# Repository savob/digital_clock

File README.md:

# Digital Clock
A hardware only digital clock project, my first embedded project without a single microcontroller involved!

Designed in a modular system to allow easy reconfiguration and expirimentation with each module. There are three modules:
1. Display module - These each carry a pair of LED seven segment character displays, their drivers, and a counter for each digit
2. Reset logic module - These recieve the data for a pair of digits and routes it through logic gates to determine if a digit needs to be reset (e.g. at 10)
3. Signal generator module - This generates the base 1 Hz signal used by the clock and provides the power for all other modules

### Small Notice
In the original designs of the reset modules I either forgot or naively didn't bother to include decoupling capacitors for the ICs. This caused the system to be incredibly suseptible to any sort of electrostatic discharge in the surrendings and throwing off the time.

This has been addressed in the newer version.

## Display Module
The main modules present; serve to house and drive two displays each as well as the counter for each digit. The digits are all standard LED seven-segment character displays and can be either common anode (CA) or common cathode (CC) types. The board can accomadate either by switching the driver chip used and a solder jumper accordingly. The left digit is referred to as the "primary" and the right one as "secondary".

The counters serve to store the value for each digit and increment it when they recieve a clock signal. When a digit "turns over" (returns to zero, resets) this is also used as the signal to increment the next digit up. The result is the count (time) is propagated right to left through the system like a normal clock. The logic to reset digits is not housed on these boards themselves, instead the signals for the value of each couter and their reset signal are routed to the bottom to be handled by the logic modules. 

## Reset Logic Module
This is responsible for "turning over" digits as needed when they reach their upper limit, 6 or 10 (with special cases for the hour digits). These have a set of four two-input AND and OR gates that are to be wired up by the user depending on the behavior desired for a given digit.

For example the ones digit for seconds needs to be reset everytime it reaches ten (10). To arrange for this the user would wire the 8 and 2 signal for that digit (8S and 2S respectively since it would be the secondary digit on that diplay) to the inputs of one of the AND gates available, then connect the output of that AND to the reset for that digit (RS). Now when it is 10 (8 + 2), the reset will be driven high and the counter will return to zero (and increment the next digit up).

## Signal Generator Module
This module serves two purposes: primarily to generate the required 1 Hz base clock for the clock, and secondarily to supply the system with the 5V required via a standard USB.

The 1 Hz signal is generated using a CD4060 chip driving a 32.768 kHz crystal and dividing down the signal by a factor of 256 to 128 Hz, which is fed into another CD4060 and divided down further by a factor of 128 to produce a steady 1 Hz that is fed into the clock.

### Software Used
KiCad EDA 6.0.1 was originally used to design all the schematics and boards. It has since been updated to KiCad 7.0.10.

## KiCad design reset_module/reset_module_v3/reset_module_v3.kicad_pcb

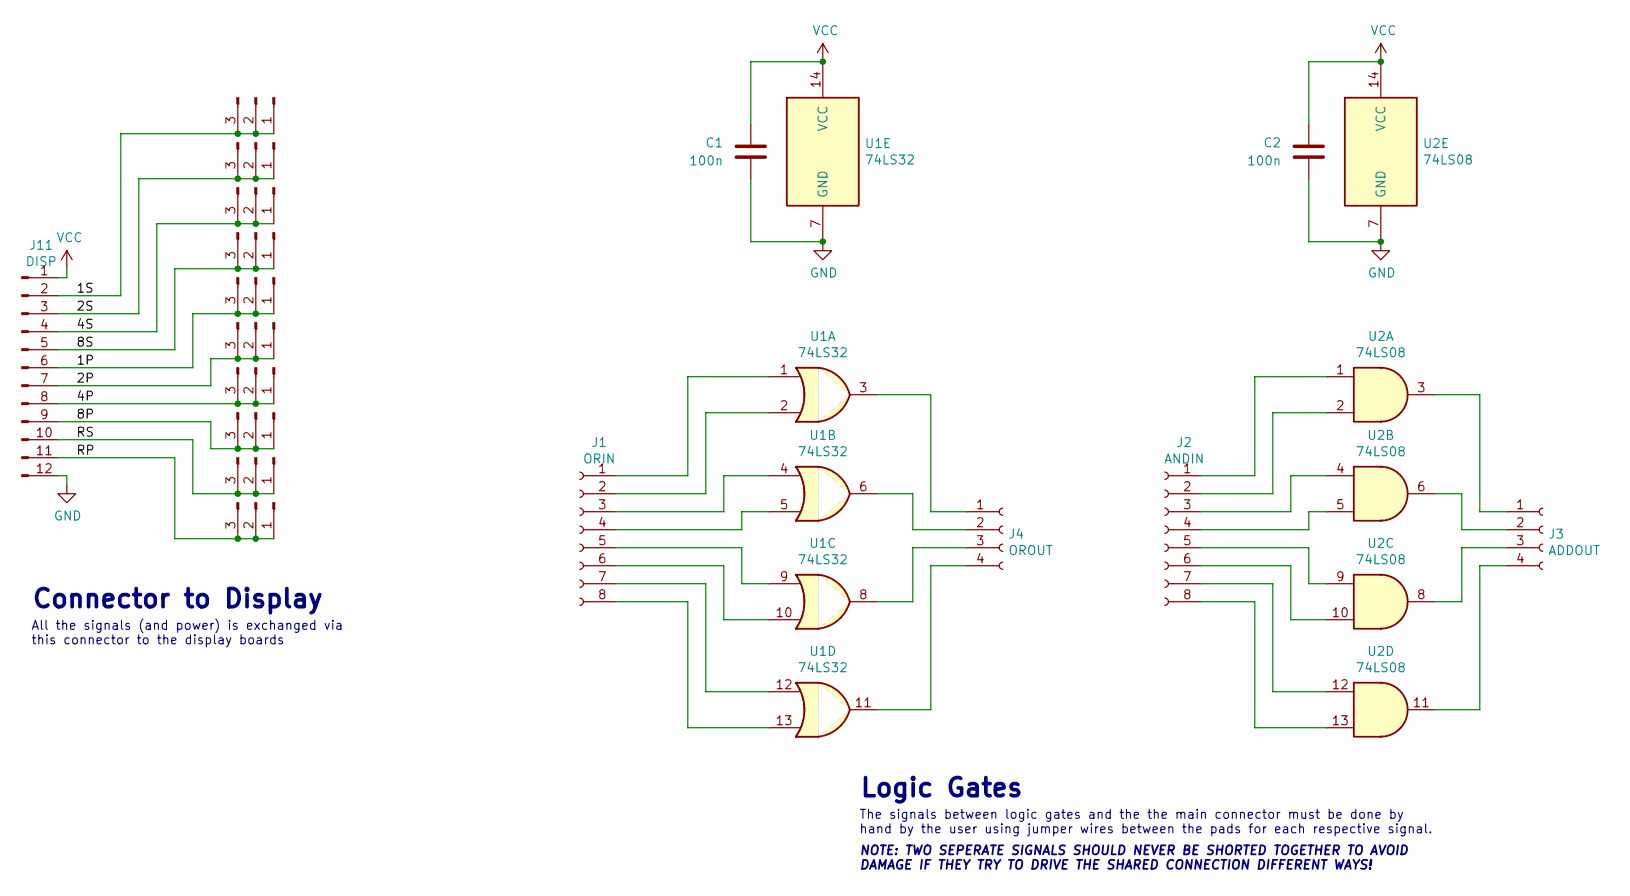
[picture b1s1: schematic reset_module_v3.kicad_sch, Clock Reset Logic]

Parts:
C1, C2: 100n; C_Disc_D3.8mm_W2.6mm_P2.50mm
J1: ORIN; PinHeader_1x08_P2.54mm_Vertical
J2: ANDIN; PinHeader_1x08_P2.54mm_Vertical
J3: ADDOUT; PinHeader_1x04_P2.54mm_Vertical
J4: OROUT; PinHeader_1x04_P2.54mm_Vertical
J5, J6, J7, J8, J9, J10, J12, J13, J14, J15: Conn_01x03_Male; PinHeader_1x03_P2.54mm_Vertical
J11: DISP; PinSocket_1x12_P2.54mm_Horizontal
U1: 74LS32; DIP-14_W7.62mm_Socket
U2: 74LS08; DIP-14_W7.62mm_Socket

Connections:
/1P: J9.1, J9.2, J9.3, J11.6
/1S: J5.1, J5.2, J5.3, J11.2
/2P: J10.1, J10.2, J10.3, J11.7
/2S: J6.1, J6.2, J6.3, J11.3
/4P: J11.8, J12.1, J12.2, J12.3
/4S: J7.1, J7.2, J7.3, J11.4
/8P: J11.9, J13.1, J13.2, J13.3
/8S: J8.1, J8.2, J8.3, J11.5
/RP: J11.11, J15.1, J15.2, J15.3
/RS: J11.10, J14.1, J14.2, J14.3
GND: C1.2, C2.2, J11.12, U1.7 (GND), U2.7 (GND)
unnamed: J1.1, U1.1
unnamed: J1.2, U1.2
unnamed: J1.3, U1.4
unnamed: J1.4, U1.5
unnamed: J1.5, U1.9
unnamed: J1.6, U1.10
unnamed: J1.7, U1.12
unnamed: J1.8, U1.13
unnamed: J2.1, U2.1
unnamed: J2.2, U2.2
unnamed: J2.3, U2.4
unnamed: J2.4, U2.5
unnamed: J2.5, U2.9
unnamed: J2.6, U2.10
unnamed: J2.7, U2.12
unnamed: J2.8, U2.13
unnamed: J3.1, U2.3
unnamed: J3.2, U2.6
unnamed: J3.3, U2.8
unnamed: J3.4, U2.11
unnamed: J4.1, U1.3
unnamed: J4.2, U1.6
unnamed: J4.3, U1.8
unnamed: J4.4, U1.11
VCC: C1.1, C2.1, J11.1, U1.14 (VCC), U2.14 (VCC)

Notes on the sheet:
Logic Gates
Connector to Display
NOTE: TWO SEPERATE SIGNALS SHOULD NEVER BE SHORTED TOGETHER TO AVOID DAMAGE IF THEY TRY TO DRIVE THE SHARED CONNECTION DIFFERENT WAYS!
The signals between logic gates and the the main connector must be done by hand by the user using jumper wires between the pads for each respective signal.
All the signals (and power) is exchanged via this connector to the display boards

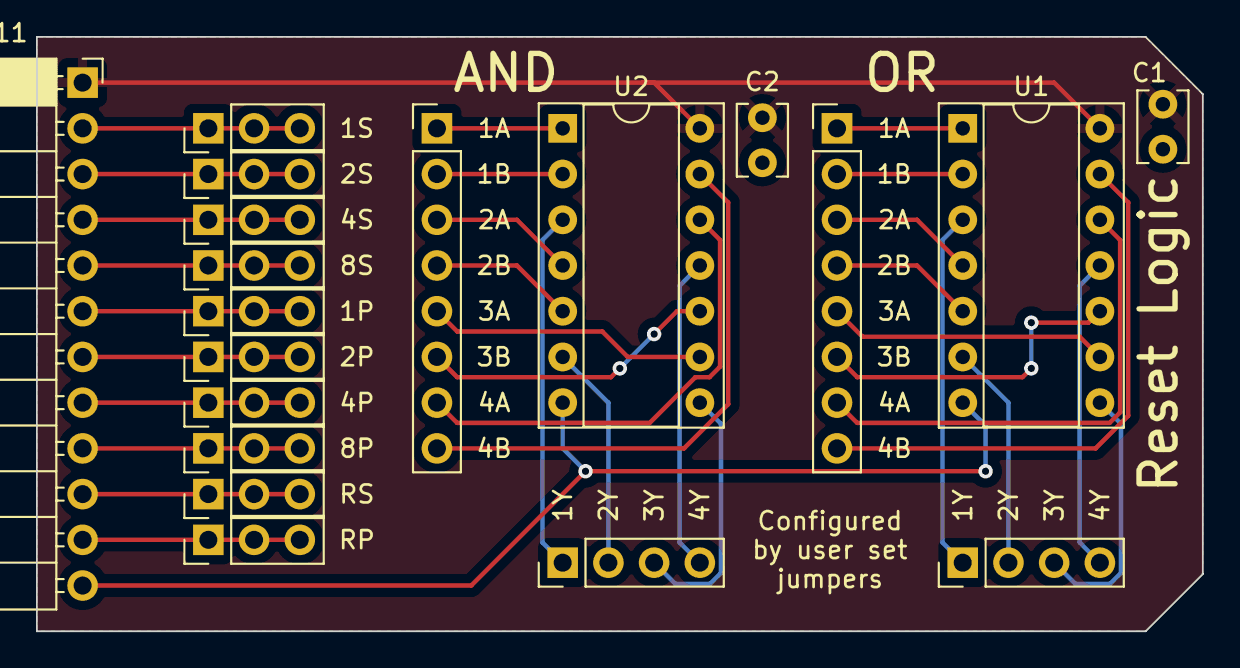
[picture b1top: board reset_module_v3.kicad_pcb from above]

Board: 2 copper layers, 64.8 x 33.0 mm, 19 parts (0 on the bottom side), 36 nets.

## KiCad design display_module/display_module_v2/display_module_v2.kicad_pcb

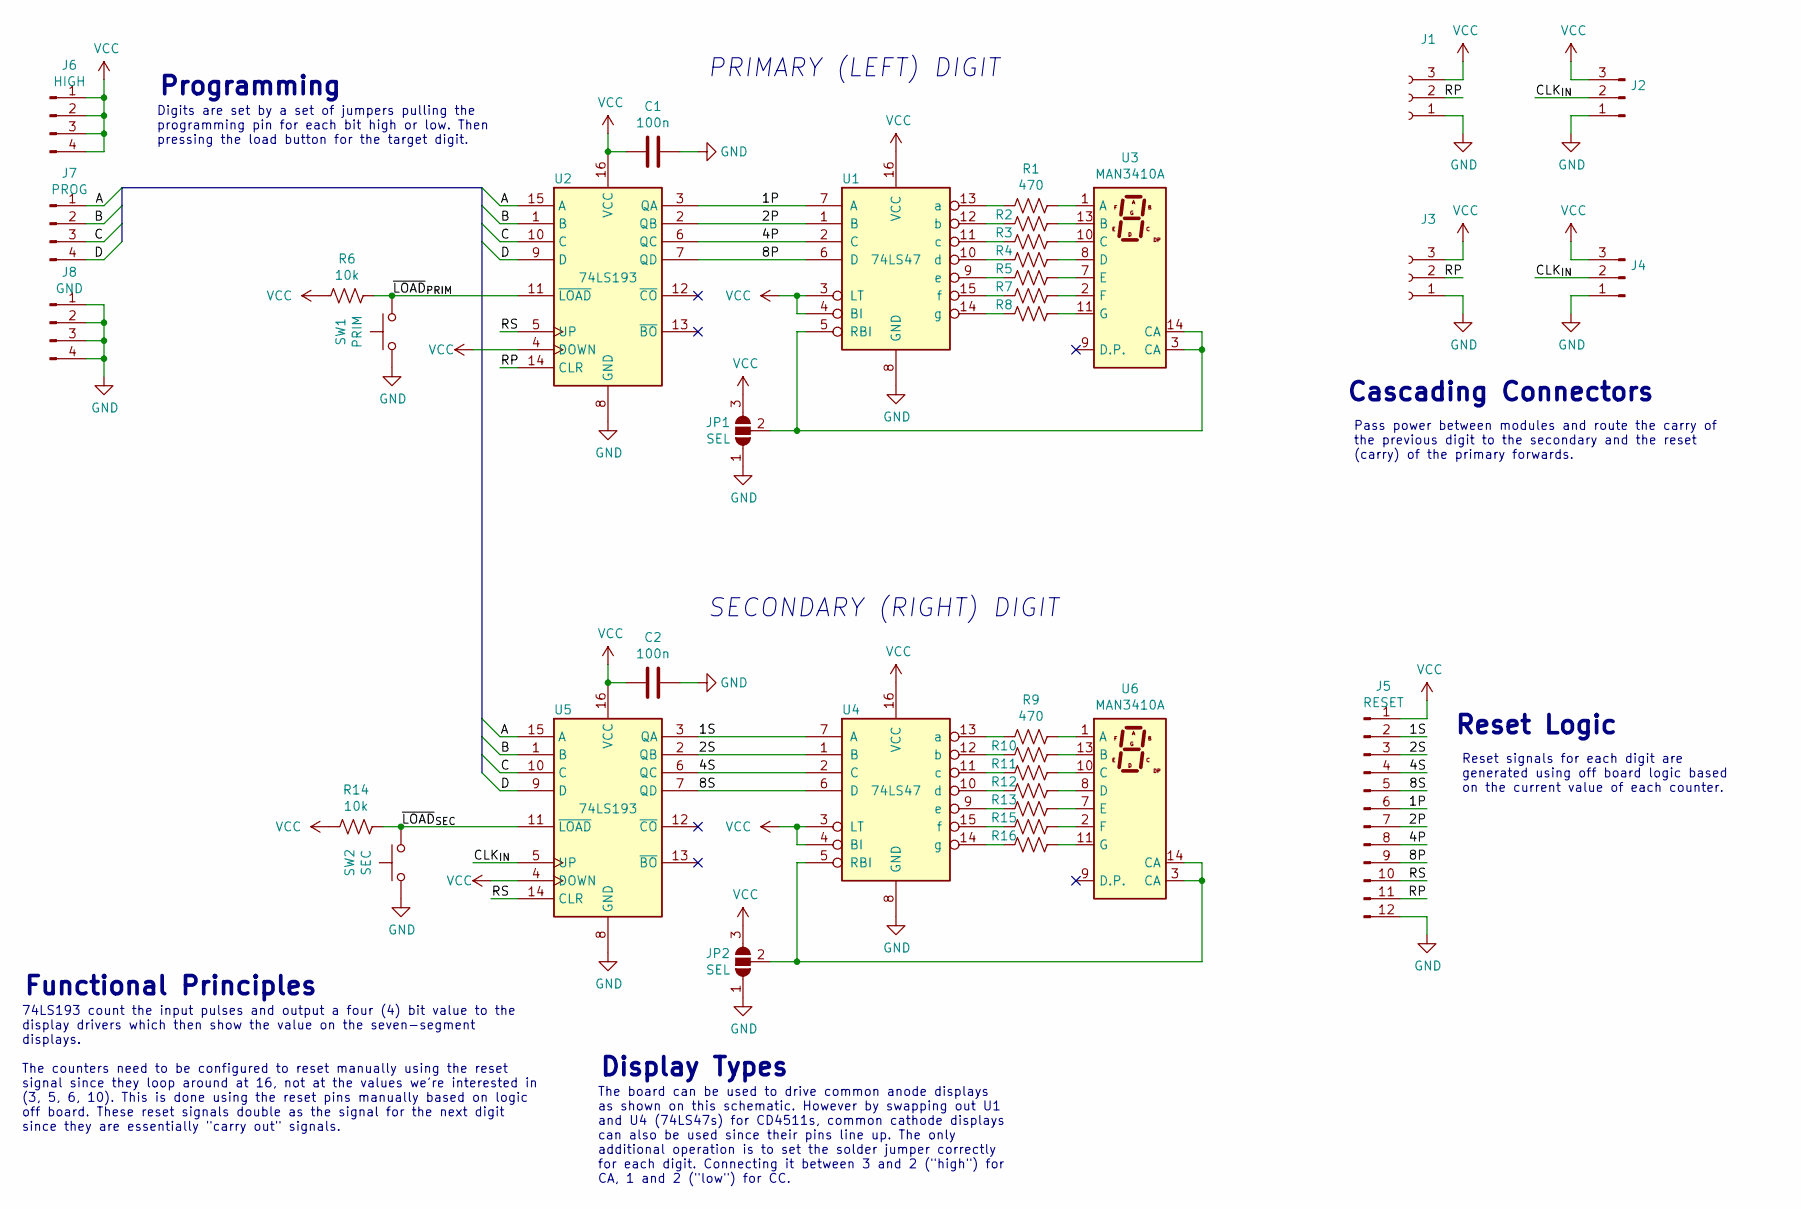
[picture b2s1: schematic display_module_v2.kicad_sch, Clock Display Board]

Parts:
C1, C2: 100n; C_Disc_D3.8mm_W2.6mm_P2.50mm
J1, J3: Conn_01x03_Female; PinSocket_1x03_P2.54mm_Horizontal
J2, J4: Conn_01x03_Male; PinHeader_1x03_P2.54mm_Horizontal
J5: RESET; PinHeader_1x12_P2.54mm_Horizontal
J6: HIGH; PinHeader_1x04_P2.54mm_Vertical
J7: PROG; PinHeader_1x04_P2.54mm_Vertical
J8: GND; PinHeader_1x04_P2.54mm_Vertical
JP1, JP2: SEL; SolderJumper-3_P1.3mm_Open_RoundedPad1.0x1.5mm
R1, R2, R3, R4, R5, R7, R8, R9, R10, R11, R12, R13, R15, R16: 470; R_Axial_DIN0207_L6.3mm_D2.5mm_P10.16mm_Horizontal
R6, R14: 10k; R_Axial_DIN0207_L6.3mm_D2.5mm_P10.16mm_Horizontal
SW1: PRIM; SW_PUSH_6mm_H4.3mm
SW2: SEC; SW_PUSH_6mm_H4.3mm
U1, U4: 74LS47; DIP-16_W7.62mm
U2, U5: 74LS193; DIP-16_W7.62mm
U3, U6: MAN3410A

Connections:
/1P: J5.6, U1.7 (A), U2.3 (QA)
/1S: J5.2, U4.7 (A), U5.3 (QA)
/2P: J5.7, U1.1 (B), U2.2 (QB)
/2S: J5.3, U4.1 (B), U5.2 (QB)
/4P: J5.8, U1.2 (C), U2.6 (QC)
/4S: J5.4, U4.2 (C), U5.6 (QC)
/8P: J5.9, U1.6 (D), U2.7 (QD)
/8S: J5.5, U4.6 (D), U5.7 (QD)
/A: J7.1, U2.15 (A), U5.15 (A)
/B: J7.2, U2.1 (B), U5.1 (B)
/C: J7.3, U2.10 (C), U5.10 (C)
/CLK_{IN}: J2.2, J4.2, U5.5 (UP)
/D: J7.4, U2.9 (D), U5.9 (D)
/RP: J1.2, J3.2, J5.11, U2.14 (CLR)
/RS: J5.10, U2.5 (UP), U5.14 (CLR)
/~LOAD_{PRIM}: R6.1, SW1.2, U2.11 (~LOAD)
/~LOAD_{SEC}: R14.1, SW2.2, U5.11 (~LOAD)
GND: C1.2, C2.2, J1.1, J2.1, J3.1, J4.1, J5.12, J8.1, J8.2, J8.3, J8.4, JP1.1 (A), JP2.1 (A), SW1.1, SW2.1, U1.8 (GND), U2.8 (GND), U4.8 (GND), U5.8 (GND)
unnamed: JP1.2 (C), U1.5 (RBI), U3.3 (CA), U3.14 (CA)
unnamed: JP2.2 (C), U4.5 (RBI), U6.3 (CA), U6.14 (CA)
unnamed: R1.1, U3.1 (A)
unnamed: R1.2, U1.13 (a)
unnamed: R2.1, U3.13 (B)
unnamed: R2.2, U1.12 (b)
unnamed: R3.1, U3.10 (C)
unnamed: R3.2, U1.11 (c)
unnamed: R4.1, U3.8 (D)
unnamed: R4.2, U1.10 (d)
unnamed: R5.1, U3.7 (E)
unnamed: R5.2, U1.9 (e)
unnamed: R7.1, U3.2 (F)
unnamed: R7.2, U1.15 (f)
unnamed: R8.1, U3.11 (G)
unnamed: R8.2, U1.14 (g)
unnamed: R9.1, U6.1 (A)
unnamed: R9.2, U4.13 (a)
unnamed: R10.1, U6.13 (B)
unnamed: R10.2, U4.12 (b)
unnamed: R11.1, U6.10 (C)
unnamed: R11.2, U4.11 (c)
unnamed: R12.1, U6.8 (D)
unnamed: R12.2, U4.10 (d)
unnamed: R13.1, U6.7 (E)
unnamed: R13.2, U4.9 (e)
unnamed: R15.1, U6.2 (F)
unnamed: R15.2, U4.15 (f)
unnamed: R16.1, U6.11 (G)
unnamed: R16.2, U4.14 (g)
VCC: C1.1, C2.1, J1.3, J2.3, J3.3, J4.3, J5.1, J6.1, J6.2, J6.3, J6.4, JP1.3 (B), JP2.3 (B), R6.2, R14.2, U1.3 (LT), U1.4 (BI), U1.16 (VCC), U2.4 (DOWN), U2.16 (VCC), U4.3 (LT), U4.4 (BI), U4.16 (VCC), U5.4 (DOWN), U5.16 (VCC)

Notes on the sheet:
Reset signals for each digit are generated using off board logic based on the current value of each counter.
Pass power between modules and route the carry of the previous digit to the secondary and the reset (carry) of the primary forwards.
74LS193 count the input pulses and output a four (4) bit value to the display drivers which then show the value on the seven-segment displays. The counters need to be configured to reset manually using the reset signal since they loop around at 16, not at the values we're interested in (3, 5, 6, 10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
Digits are set by a set of jumpers pulling the programming pin for each bit high or low. Then pressing the load button for the target digit.
The board can be used to drive common anode displays as shown on this schematic. However by swapping out U1 and U4 (74LS47s) for CD4511s, common cathode displays can also be used since their pins line up. The only additional operation is to set the solder jumper correctly for each digit. Connecting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
Functional Principles
Programming
PRIMARY (LEFT) DIGIT
Reset Logic
SECONDARY (RIGHT) DIGIT
Display Types
Cascading Connectors

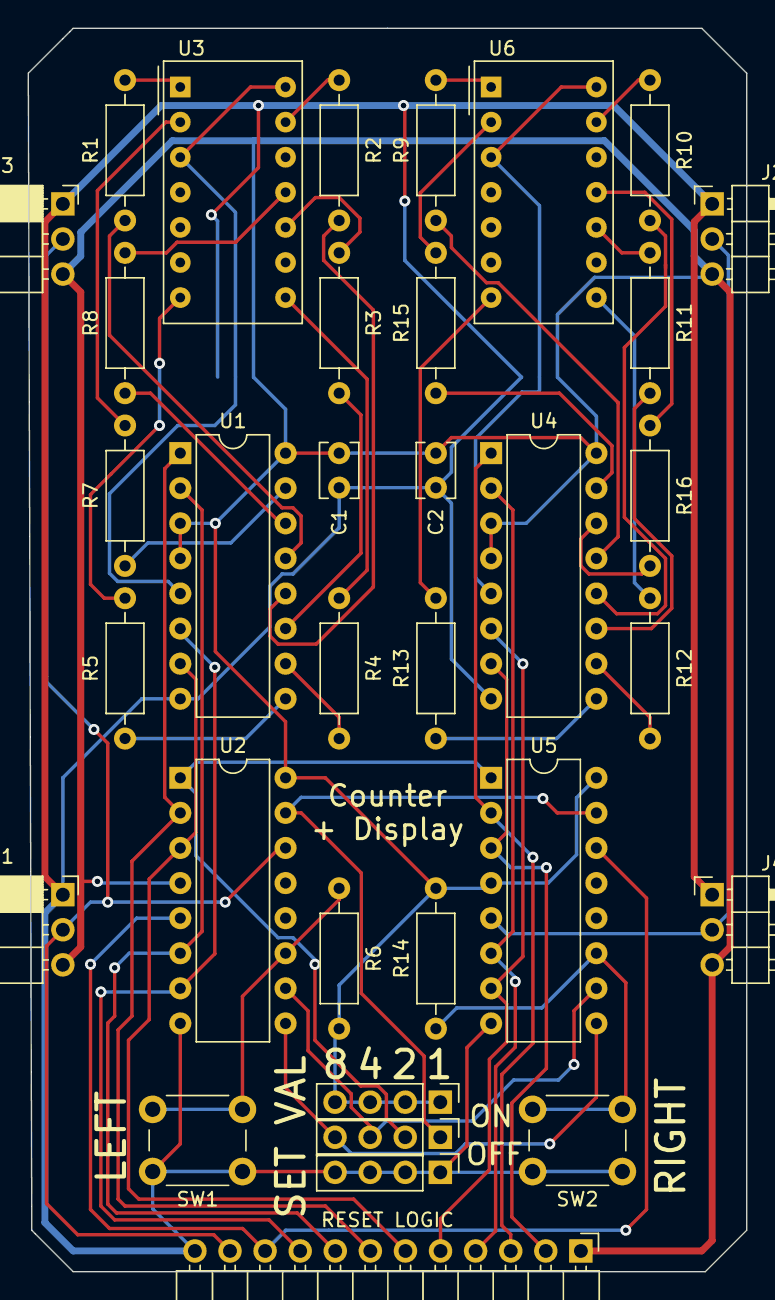
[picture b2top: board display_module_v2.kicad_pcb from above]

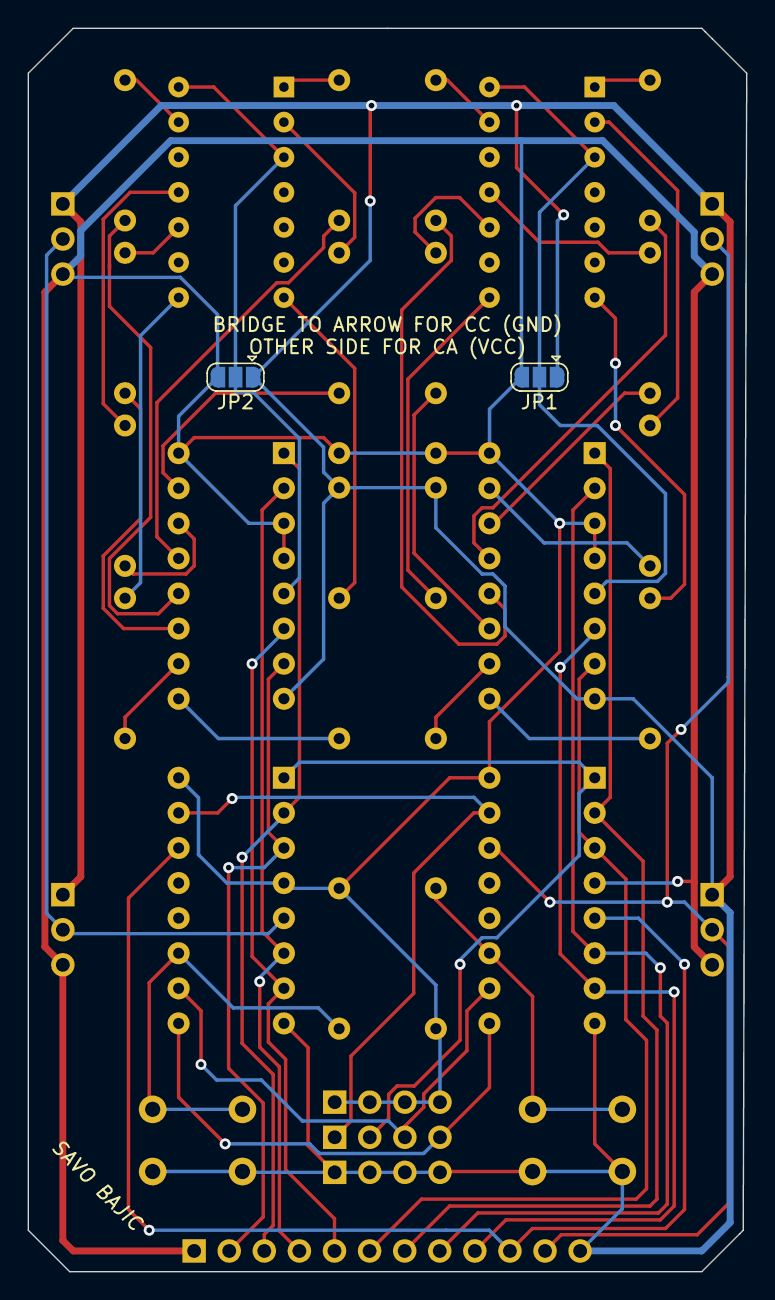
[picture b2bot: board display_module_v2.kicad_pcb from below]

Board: 2 copper layers, 52.0 x 90.0 mm, 36 parts (2 on the bottom side), 49 nets.

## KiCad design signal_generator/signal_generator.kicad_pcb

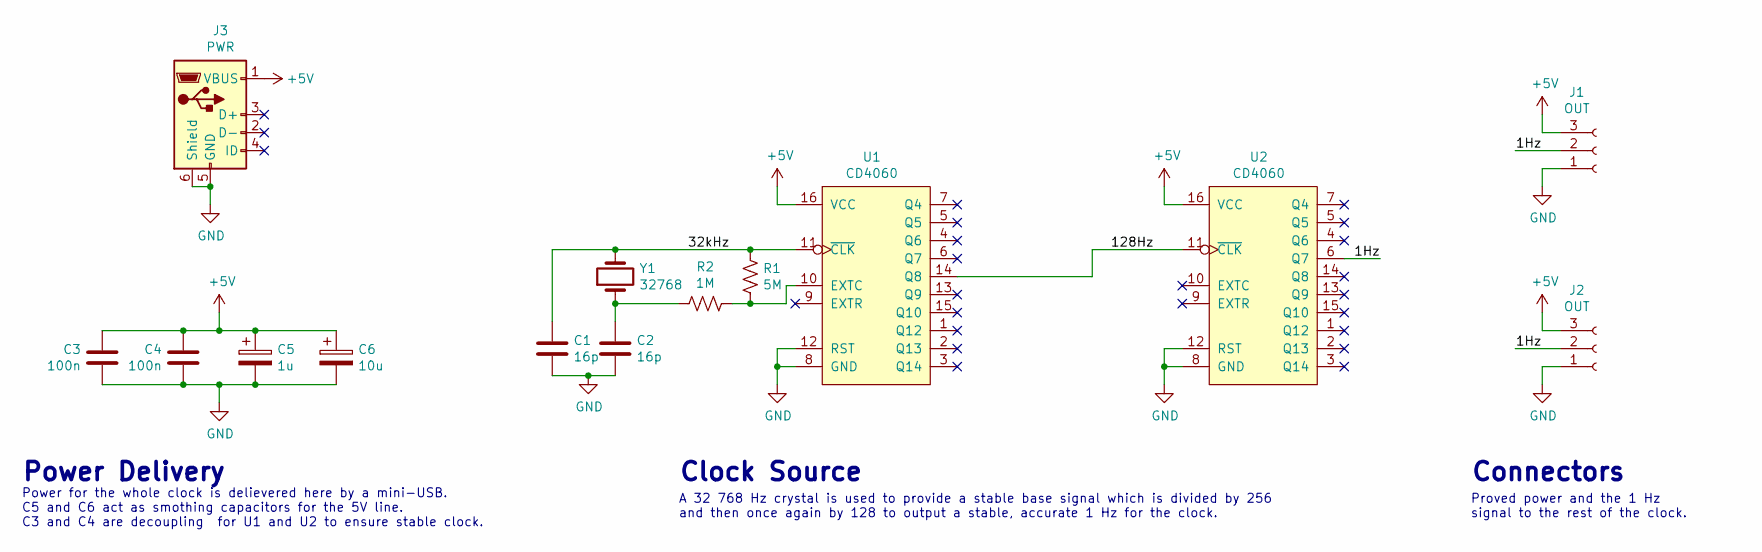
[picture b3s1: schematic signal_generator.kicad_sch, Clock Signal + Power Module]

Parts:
C1, C2: 16p; C_Disc_D3.4mm_W2.1mm_P2.50mm
C3, C4: 100n; C_Disc_D3.0mm_W2.0mm_P2.50mm
C5: 1u; CP_Radial_D4.0mm_P2.00mm
C6: 10u; CP_Radial_D4.0mm_P2.00mm
J1, J2: OUT; PinSocket_1x03_P2.54mm_Horizontal
J3: PWR; TE_2172034-1
R1: 5M; R_Axial_DIN0207_L6.3mm_D2.5mm_P10.16mm_Horizontal
R2: 1M; R_Axial_DIN0207_L6.3mm_D2.5mm_P10.16mm_Horizontal
U1, U2: CD4060; DIP-16_W7.62mm
Y1: 32768; Crystal_DS15_D1.5mm_L5.0mm_Horizontal

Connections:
+5V: C3.2, C4.2, C5.1, C6.1, J1.3, J2.3, J3.1 (VBUS), U1.16 (VCC), U2.16 (VCC)
/1Hz: J1.2, J2.2, U2.6 (Q7)
/32kHz: C1.1, R1.2, U1.11 (~CLK), Y1.2
/128Hz: U1.14 (Q8), U2.11 (~CLK)
GND: C1.2, C2.2, C3.1, C4.1, C5.2, C6.2, J1.1, J2.1, J3.5 (GND), J3.6 (Shield), U1.8 (GND), U1.12 (RST), U2.8 (GND), U2.12 (RST)
unnamed: C2.1, R2.1, Y1.1
unnamed: R1.1, R2.2, U1.10 (EXTC)

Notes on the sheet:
Power Delivery
Clock Source
Proved power and the 1 Hz signal to the rest of the clock.
A 32 768 Hz crystal is used to provide a stable base signal which is divided by 256 and then once again by 128 to output a stable, accurate 1 Hz for the clock.
Connectors
Power for the whole clock is delievered here by a mini-USB. C5 and C6 act as smothing capacitors for the 5V line. C3 and C4 are decoupling for U1 and U2 to ensure stable clock.

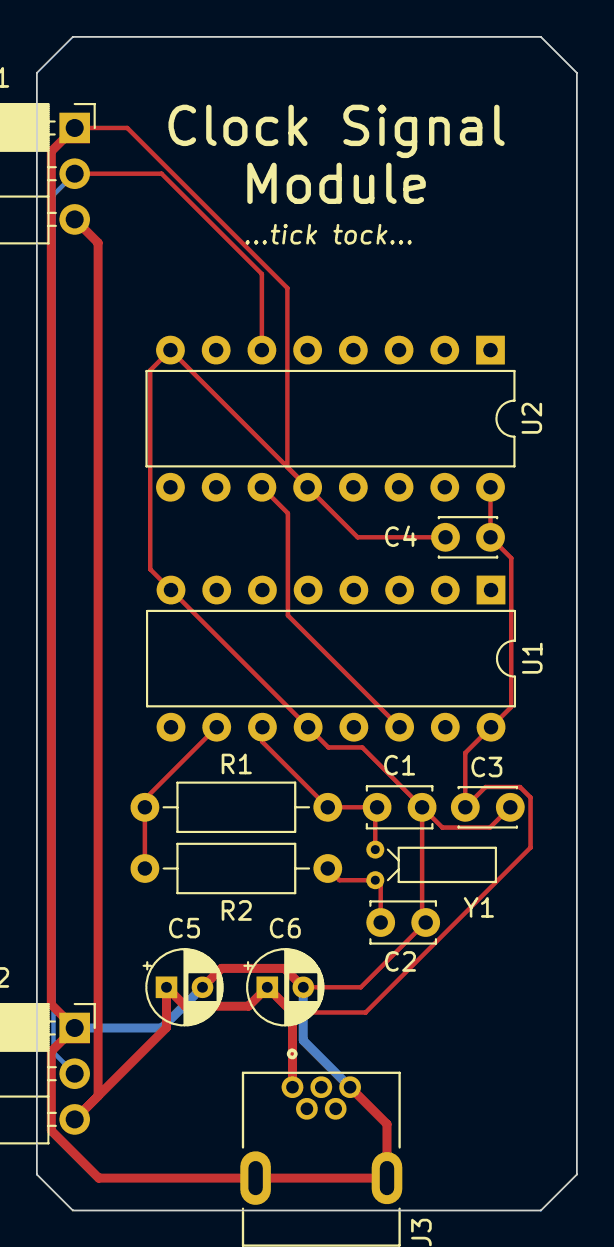
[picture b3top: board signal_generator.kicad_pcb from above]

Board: 2 copper layers, 30.0 x 65.2 mm, 14 parts (0 on the bottom side), 7 nets.

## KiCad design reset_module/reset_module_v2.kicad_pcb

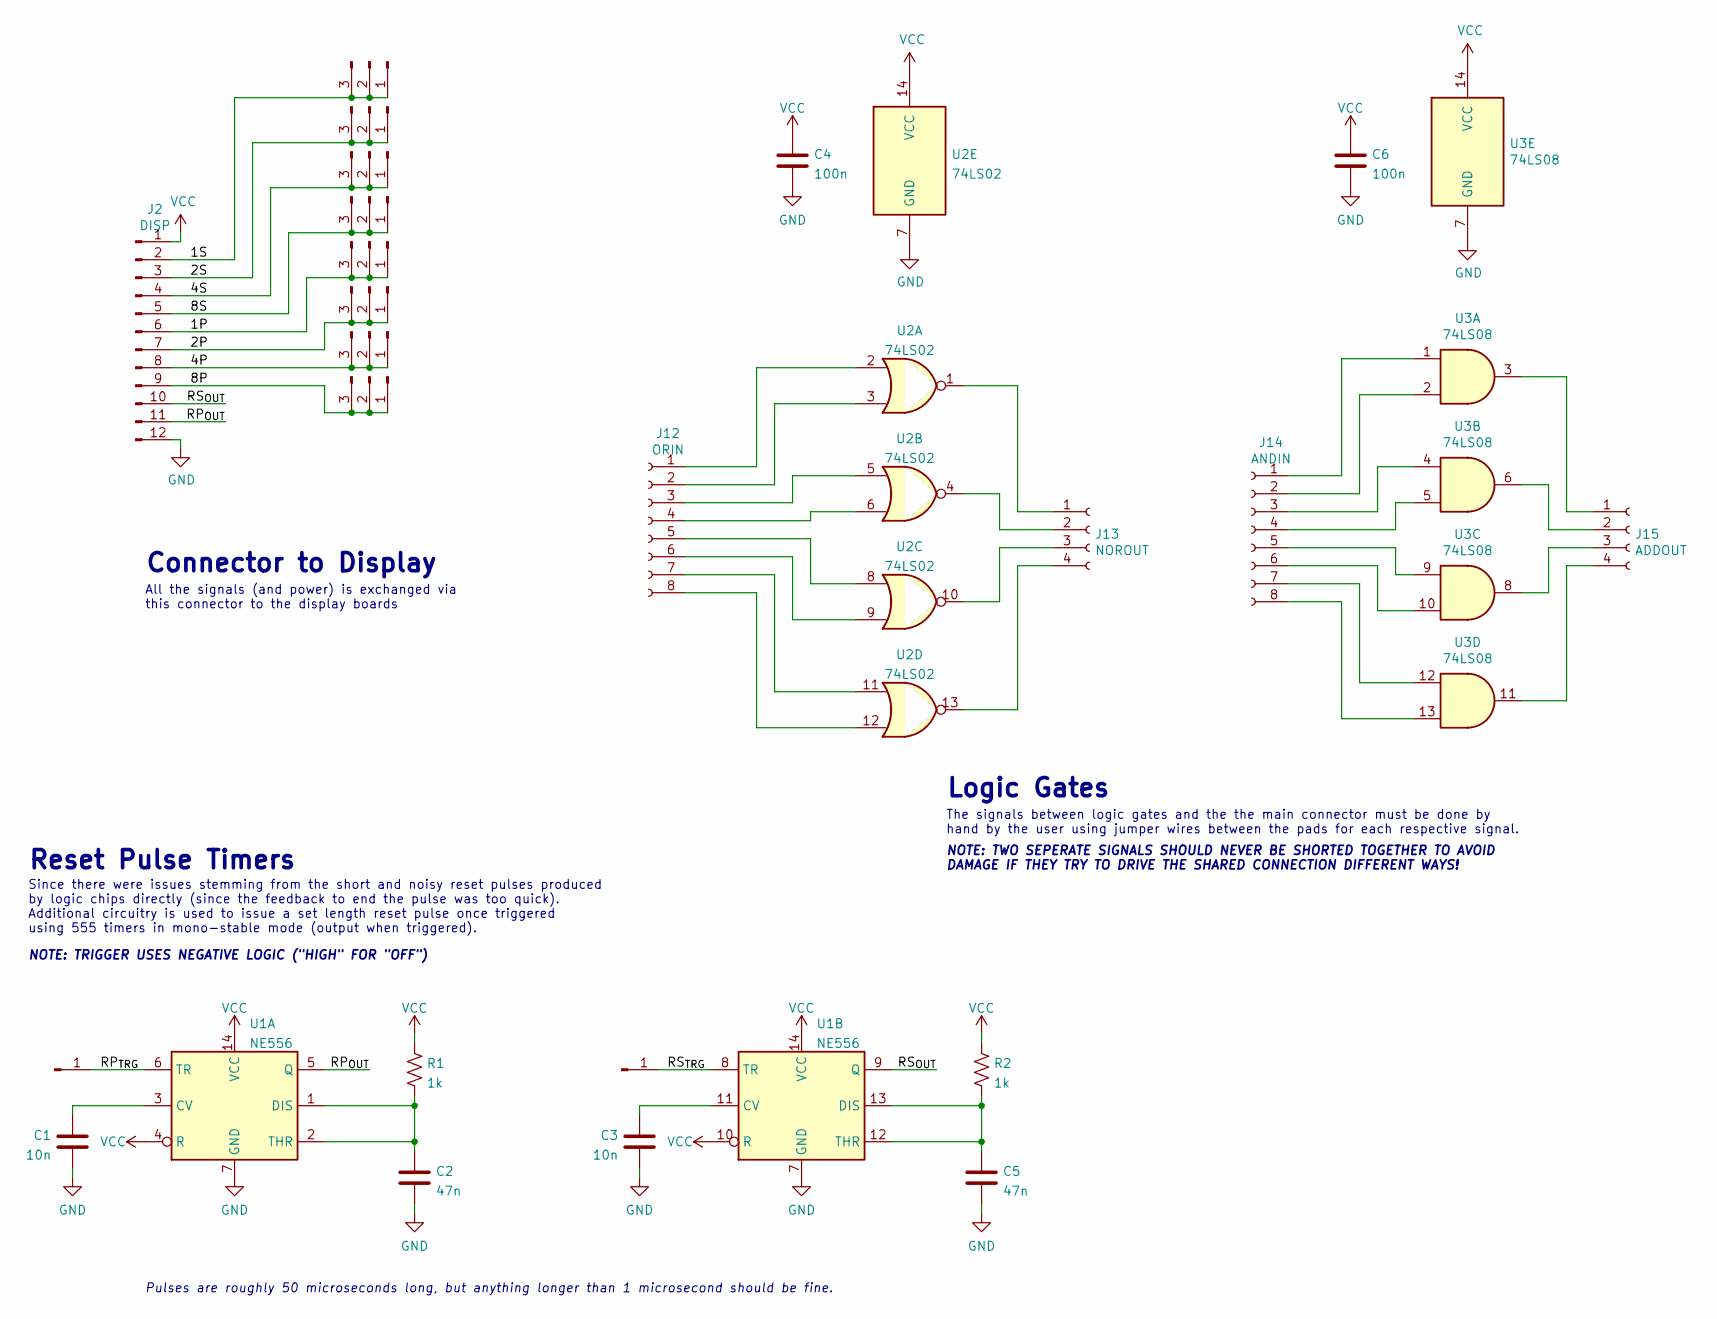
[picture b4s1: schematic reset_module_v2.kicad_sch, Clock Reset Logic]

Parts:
C1, C3: 10n; C_Disc_D5.0mm_W2.5mm_P2.50mm
C2, C5: 47n; C_Disc_D5.0mm_W2.5mm_P2.50mm
C4, C6: 100n; C_Disc_D5.0mm_W2.5mm_P2.50mm
J1: RP_{TRIGGER}; PinHeader_1x01_P2.54mm_Vertical
J2: DISP; PinSocket_1x12_P2.54mm_Horizontal
J3, J4, J5, J6, J7, J8, J9, J10: Conn_01x03_Male; PinHeader_1x03_P2.54mm_Vertical
J11: RS_{TRIGGER}; PinHeader_1x01_P2.54mm_Vertical
J12: ORIN; PinHeader_1x08_P2.54mm_Vertical
J13: NOROUT; PinHeader_1x04_P2.54mm_Vertical
J14: ANDIN; PinHeader_1x08_P2.54mm_Vertical
J15: ADDOUT; PinHeader_1x04_P2.54mm_Vertical
R1, R2: 1k; R_Axial_DIN0207_L6.3mm_D2.5mm_P10.16mm_Horizontal
U1: NE556; DIP-14_W7.62mm
U2: 74LS02; DIP-14_W7.62mm
U3: 74LS08; DIP-14_W7.62mm

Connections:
/1P: J2.6, J7.1, J7.2, J7.3
/1S: J2.2, J3.1, J3.2, J3.3
/2P: J2.7, J8.1, J8.2, J8.3
/2S: J2.3, J4.1, J4.2, J4.3
/4P: J2.8, J9.1, J9.2, J9.3
/4S: J2.4, J5.1, J5.2, J5.3
/8P: J2.9, J10.1, J10.2, J10.3
/8S: J2.5, J6.1, J6.2, J6.3
/RP_{OUT}: J2.11, U1.5 (Q)
/RP_{TRG}: J1.1, U1.6 (TR)
/RS_{OUT}: J2.10, U1.9 (Q)
/RS_{TRG}: J11.1, U1.8 (TR)
GND: C1.1, C2.2, C3.1, C4.2, C5.2, C6.2, J2.12, U1.7 (GND), U2.7 (GND), U3.7 (GND)
unnamed: C1.2, U1.3 (CV)
unnamed: C2.1, R1.2, U1.1 (DIS), U1.2 (THR)
unnamed: C3.2, U1.11 (CV)
unnamed: C5.1, R2.2, U1.12 (THR), U1.13 (DIS)
unnamed: J12.1, U2.2
unnamed: J12.2, U2.3
unnamed: J12.3, U2.5
unnamed: J12.4, U2.6
unnamed: J12.5, U2.8
unnamed: J12.6, U2.9
unnamed: J12.7, U2.11
unnamed: J12.8, U2.12
unnamed: J13.1, U2.1
unnamed: J13.2, U2.4
unnamed: J13.3, U2.10
unnamed: J13.4, U2.13
unnamed: J14.1, U3.1
unnamed: J14.2, U3.2
unnamed: J14.3, U3.4
unnamed: J14.4, U3.5
unnamed: J14.5, U3.9
unnamed: J14.6, U3.10
unnamed: J14.7, U3.12
unnamed: J14.8, U3.13
unnamed: J15.1, U3.3
unnamed: J15.2, U3.6
unnamed: J15.3, U3.8
unnamed: J15.4, U3.11
VCC: C4.1, C6.1, J2.1, R1.1, R2.1, U1.4 (R), U1.10 (R), U1.14 (VCC), U2.14 (VCC), U3.14 (VCC)

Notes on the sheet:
Since there were issues stemming from the short and noisy reset pulses produced by logic chips directly (since the feedback to end the pulse was too quick). Additional circuitry is used to issue a set length reset pulse once triggered using 555 timers in mono-stable mode (output when triggered).
Logic Gates
Connector to Display
NOTE: TWO SEPERATE SIGNALS SHOULD NEVER BE SHORTED TOGETHER TO AVOID DAMAGE IF THEY TRY TO DRIVE THE SHARED CONNECTION DIFFERENT WAYS!
The signals between logic gates and the the main connector must be done by hand by the user using jumper wires between the pads for each respective signal.
NOTE: TRIGGER USES NEGATIVE LOGIC ("HIGH" FOR "OFF")
Reset Pulse Timers
All the signals (and power) is exchanged via this connector to the display boards
Pulses are roughly 50 microseconds long, but anything longer than 1 microsecond should be fine.

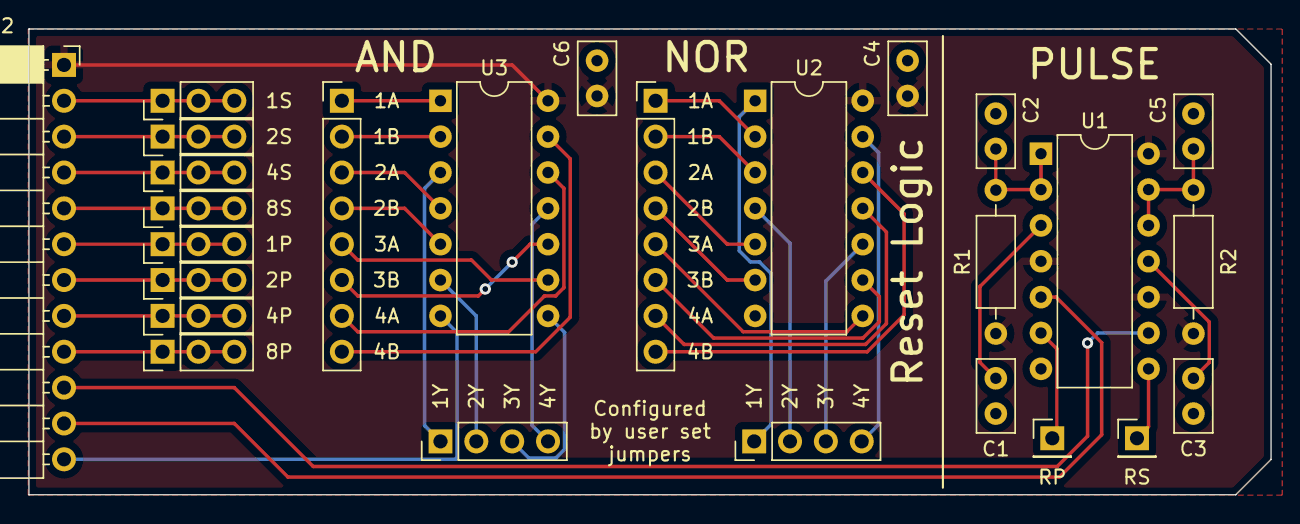
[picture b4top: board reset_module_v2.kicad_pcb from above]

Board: 2 copper layers, 88.0 x 33.0 mm, 26 parts (0 on the bottom side), 42 nets.

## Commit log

2021-12-03 Initial upload of hardware files
2021-12-03 Described the modules
2021-12-03 Uploaded renders of each board
2021-12-03 Reupload of media
    Removed spaces from file names
2021-12-03 Media reupload
    Removed spaces from file names
2021-12-03 Added images to readme
2021-12-04 Fixed some grammar and added some clarification
2022-02-15 Migrated to KiCad 6
2022-02-15 Prepared gerber files for manufacture
    Also added dimensions to board layout files
2022-03-25 New schematics and minor rev for display
    Added a signal name to the display board for the data load signals for each counter.
2022-03-29 Added revised reset module files
2024-01-04 Added licence
2024-01-04 Reorganization
2024-01-04 Added
2024-01-04 Added decoupling capacitors to reset module
